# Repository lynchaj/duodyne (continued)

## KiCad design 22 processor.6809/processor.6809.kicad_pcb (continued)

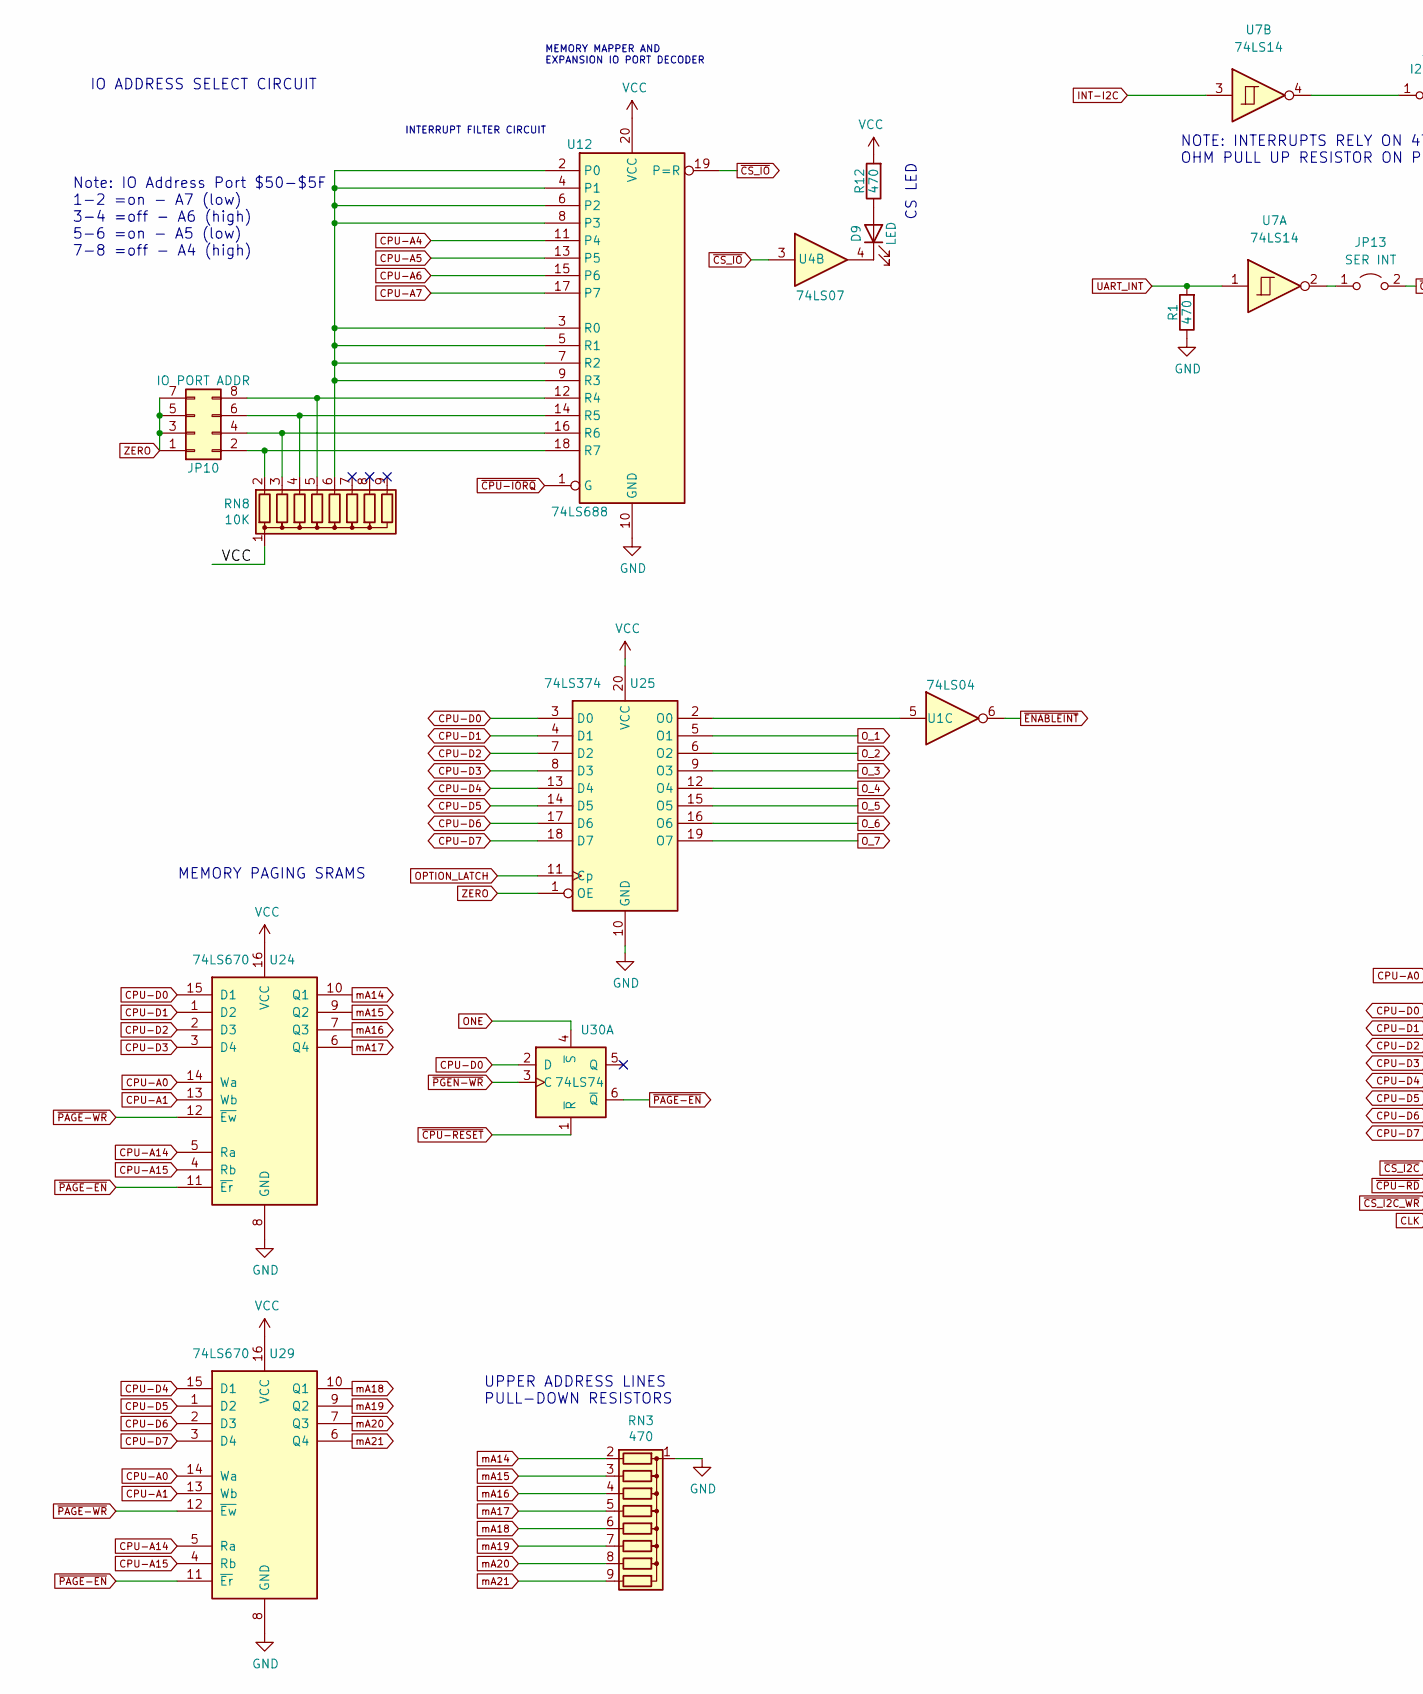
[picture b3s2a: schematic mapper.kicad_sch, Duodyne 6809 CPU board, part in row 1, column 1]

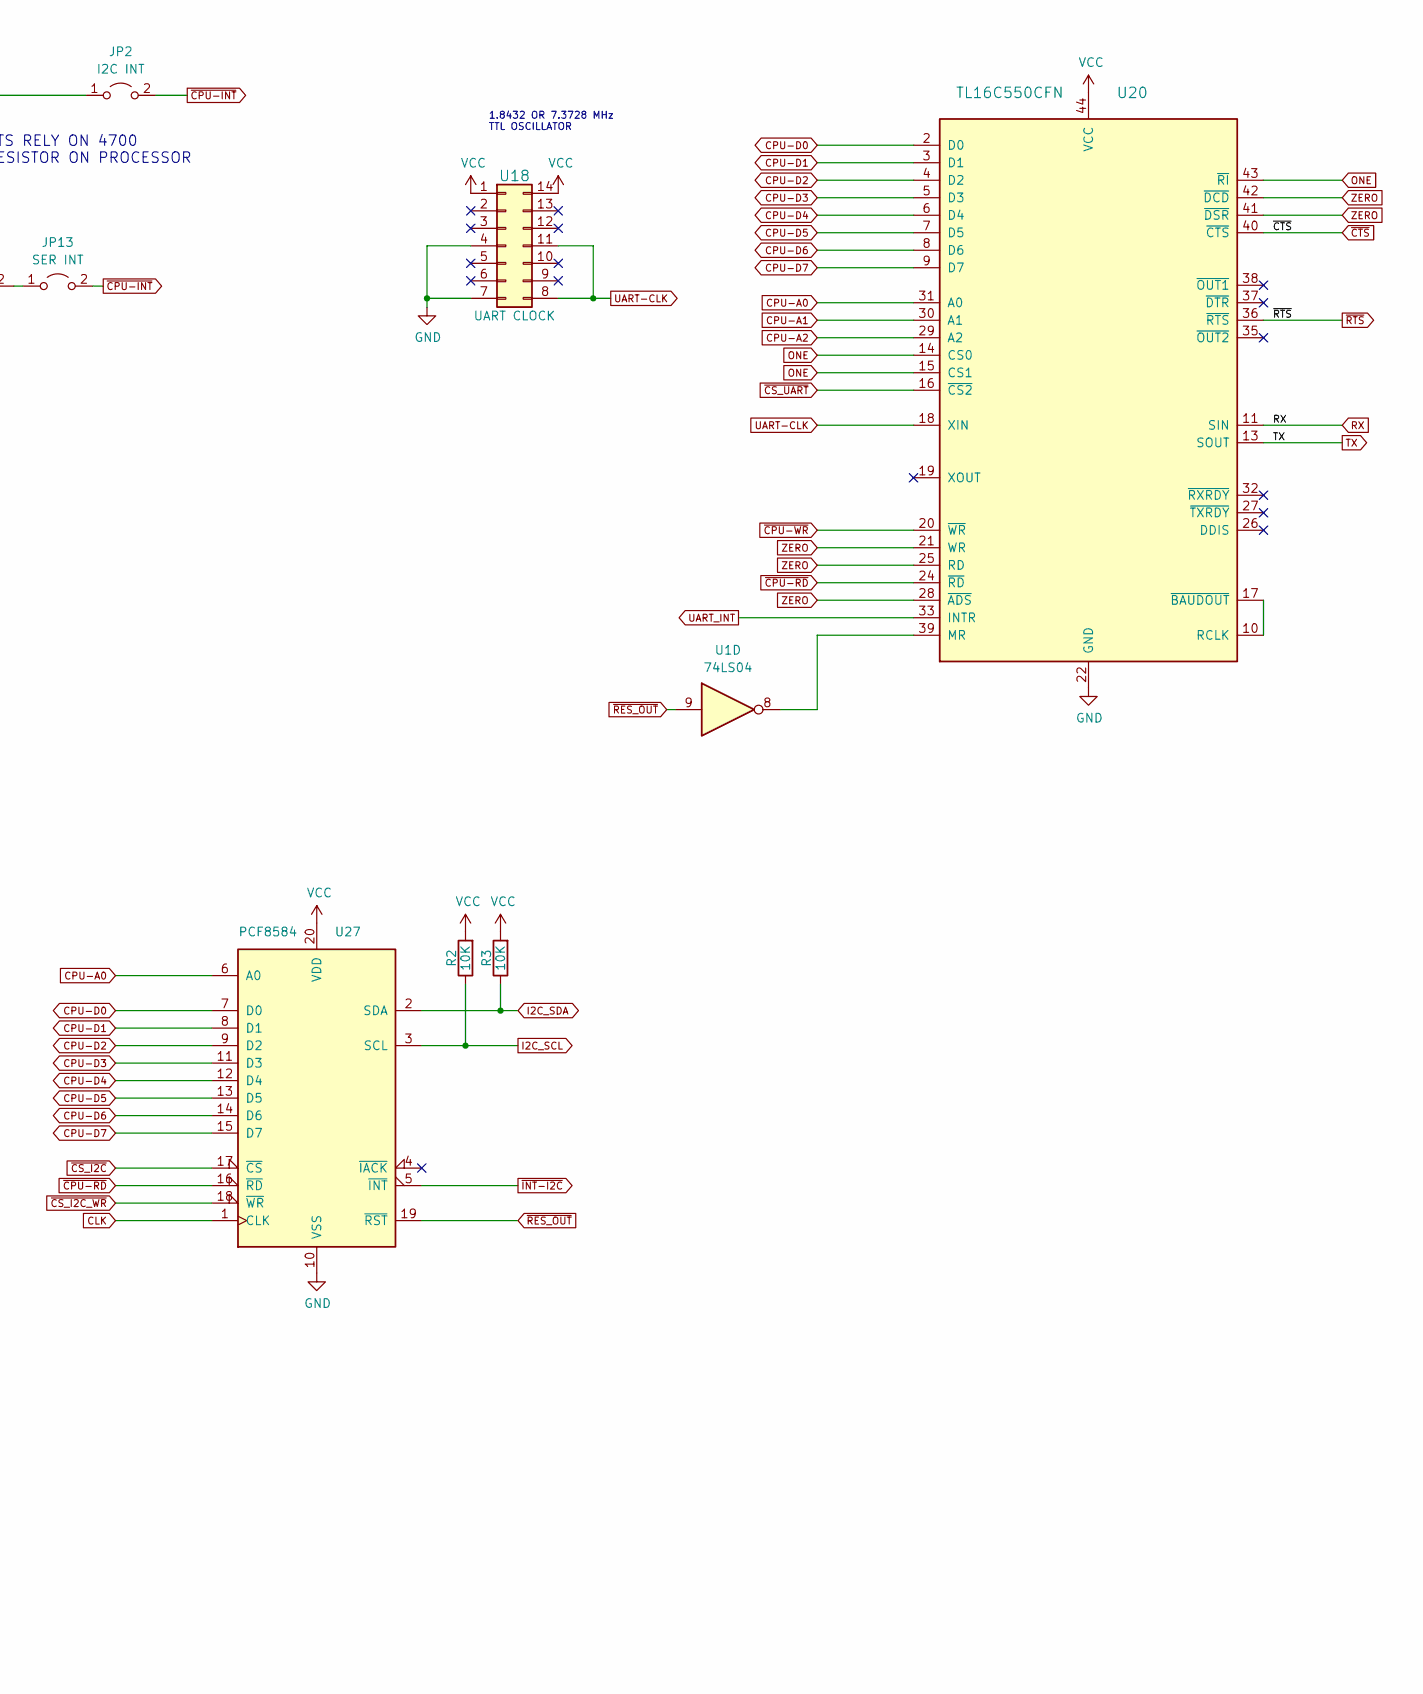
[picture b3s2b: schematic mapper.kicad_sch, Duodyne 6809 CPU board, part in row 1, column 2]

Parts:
D9: LED; LED_D3.0mm_Horizontal_O3.81mm_Z2.0mm
JP2: I2C INT; PinHeader_1x02_P2.54mm_Vertical
JP10: IO PORT ADDR; PinHeader_2x04_P2.54mm_Vertical
JP13: SER INT; PinHeader_1x02_P2.54mm_Vertical
R1, R12: 470; R_Axial_DIN0207_L6.3mm_D2.5mm_P7.62mm_Horizontal
R2, R3: 10K; R_Axial_DIN0207_L6.3mm_D2.5mm_P7.62mm_Horizontal
RN3: 470; R_Array_SIP9
RN8: 10K; R_Array_SIP9
U1: 74LS04; DIP-14_W7.62mm_Socket_LongPads
U4: 74LS07; DIP-14_W7.62mm_Socket_LongPads
U7: 74LS14; DIP-14_W7.62mm_Socket_LongPads
U12: 74LS688; DIP-20_W7.62mm_Socket_LongPads
U18: UART CLOCK; DIP-14_W7.62mm_Socket_LongPads
U20: TL16C550CFN; PLCC-44_THT-Socket
U24, U29: 74LS670; DIP-16_W7.62mm
U25: 74LS374; DIP-20_W7.62mm_Socket_LongPads
U27: PCF8584; DIP-20_W7.62mm_Socket_LongPads
U30: 74LS74; DIP-14_W7.62mm

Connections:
CLK: U27.1 (CLK); also elsewhere on the board
CPU-A0: U20.31 (A0), U24.14 (Wa), U27.6 (A0), U29.14 (Wa); also elsewhere on the board
CPU-A1: U20.30 (A1), U24.13 (Wb), U29.13 (Wb); also elsewhere on the board
CPU-A2: U20.29 (A2); also elsewhere on the board
CPU-A4: U12.11 (P4); also elsewhere on the board
CPU-A5: U12.13 (P5); also elsewhere on the board
CPU-A6: U12.15 (P6); also elsewhere on the board
CPU-A7: U12.17 (P7); also elsewhere on the board
CPU-A14: U24.5 (Ra), U29.5 (Ra); also elsewhere on the board
CPU-A15: U24.4 (Rb), U29.4 (Rb); also elsewhere on the board
CPU-D0: U20.2 (D0), U24.15 (D1), U25.3 (D0), U27.7 (D0), U30.2 (D); also elsewhere on the board
CPU-D1: U20.3 (D1), U24.1 (D2), U25.4 (D1), U27.8 (D1); also elsewhere on the board
CPU-D2: U20.4 (D2), U24.2 (D3), U25.7 (D2), U27.9 (D2); also elsewhere on the board
CPU-D3: U20.5 (D3), U24.3 (D4), U25.8 (D3), U27.11 (D3); also elsewhere on the board
CPU-D4: U20.6 (D4), U25.13 (D4), U27.12 (D4), U29.15 (D1); also elsewhere on the board
CPU-D5: U20.7 (D5), U25.14 (D5), U27.13 (D5), U29.1 (D2); also elsewhere on the board
CPU-D6: U20.8 (D6), U25.17 (D6), U27.14 (D6), U29.2 (D3); also elsewhere on the board
CPU-D7: U20.9 (D7), U25.18 (D7), U27.15 (D7), U29.3 (D4); also elsewhere on the board
GND: R1.1, RN3.1 (common), U12.10 (GND), U18.4, U18.7, U20.22 (GND), U24.8 (GND), U25.10 (GND), U27.10 (VSS), U29.8 (GND); also elsewhere on the board
I2C_SCL: R2.1, U27.3 (SCL); also elsewhere on the board
I2C_SDA: R3.1, U27.2 (SDA); also elsewhere on the board
INT-I2C: U7.3; also elsewhere on the board
unnamed: D9.1 (K), U4.4
unnamed: D9.2 (A), R12.1
unnamed: JP2.1 (A), U7.4
unnamed: JP10.2, RN8.2 (R1), U12.18 (R7)
unnamed: JP10.4, RN8.3 (R2), U12.16 (R6)
unnamed: JP10.6, RN8.4 (R3), U12.14 (R5)
unnamed: JP10.8, RN8.5 (R4), U12.12 (R4)
unnamed: JP13.1 (A), U7.2
unnamed: RN8.6 (R5), U12.2 (P0), U12.3 (R0), U12.4 (P1), U12.5 (R1), U12.6 (P2), U12.7 (R2), U12.8 (P3), U12.9 (R3)
unnamed: U1.5, U25.2 (O0)
unnamed: U1.8, U20.39 (MR)
unnamed: U20.10 (RCLK), U20.17 (~BAUDOUT)
ONE: U20.14 (CS0), U20.15 (CS1), U20.43 (~RI), U30.4 (~S); also elsewhere on the board
OPTION_LATCH: U25.11 (Cp); also elsewhere on the board
O_1: U25.5 (O1); also elsewhere on the board
O_2: U25.6 (O2); also elsewhere on the board
O_3: U25.9 (O3); also elsewhere on the board
O_4: U25.12 (O4); also elsewhere on the board
O_5: U25.15 (O5); also elsewhere on the board
O_6: U25.16 (O6); also elsewhere on the board
O_7: U25.19 (O7); also elsewhere on the board
RX: U20.11 (SIN); also elsewhere on the board
TX: U20.13 (SOUT); also elsewhere on the board
UART-CLK: U18.8, U18.11, U20.18 (XIN)
UART_INT: R1.2, U7.1, U20.33 (INTR)
VCC: R2.2, R3.2, R12.2, RN8.1 (common), U12.20 (VCC), U18.1, U18.14, U20.44 (VCC), U24.16 (VCC), U25.20 (VCC), U27.20 (VDD), U29.16 (VCC); also elsewhere on the board
ZERO: JP10.1, JP10.3, JP10.5, JP10.7, U20.21 (WR), U20.25 (RD), U20.28 (~ADS), U20.41 (~DSR), U20.42 (~DCD), U25.1 (OE); also elsewhere on the board
mA14: RN3.2 (R1), U24.10 (Q1); also elsewhere on the board
mA15: RN3.3 (R2), U24.9 (Q2); also elsewhere on the board
mA16: RN3.4 (R3), U24.7 (Q3); also elsewhere on the board
mA17: RN3.5 (R4), U24.6 (Q4); also elsewhere on the board
mA18: RN3.6 (R5), U29.10 (Q1); also elsewhere on the board
mA19: RN3.7 (R6), U29.9 (Q2); also elsewhere on the board
mA20: RN3.8 (R7), U29.7 (Q3); also elsewhere on the board
mA21: RN3.9 (R8), U29.6 (Q4); also elsewhere on the board
~CPU-INT: JP2.2 (B), JP13.2 (B); also elsewhere on the board
~CPU-IORQ: U12.1 (G); also elsewhere on the board
~CPU-RD: U20.24 (~RD), U27.16 (~RD); also elsewhere on the board
~CPU-RESET: U30.1 (~R); also elsewhere on the board
~CPU-WR: U20.20 (~WR); also elsewhere on the board
~CS_I2C_WR: U27.18 (~WR); also elsewhere on the board
~CS_I2C: U27.17 (~CS); also elsewhere on the board
~CS_IO: U4.3, U12.19 (P=R); also elsewhere on the board
~CS_UART: U20.16 (~CS2); also elsewhere on the board
~CTS: U20.40 (~CTS); also elsewhere on the board
~ENABLEINT: U1.6; also elsewhere on the board
~INT-I2C: U27.5 (~INT); also elsewhere on the board
~PAGE-EN: U24.11 (~Er), U29.11 (~Er), U30.6 (~Q); also elsewhere on the board
~PAGE-WR: U24.12 (~Ew), U29.12 (~Ew); also elsewhere on the board
~PGEN-WR: U30.3 (C); also elsewhere on the board
~RES_OUT: U1.9, U27.19 (~RST); also elsewhere on the board
~RTS: U20.36 (~RTS); also elsewhere on the board

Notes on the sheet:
MEMORY MAPPER AND EXPANSION IO PORT DECODER
CS LED
IO ADDRESS SELECT CIRCUIT
INTERRUPT FILTER CIRCUIT
NOTE: INTERRUPTS RELY ON 4700 OHM PULL UP RESISTOR ON PROCESSOR
Note: IO Address Port $50-$5F 1-2 =on - A7 (low) 3-4 =off - A6 (high) 5-6 =on - A5 (low) 7-8 =off - A4 (high)
MEMORY PAGING SRAMS
1.8432 OR 7.3728 MHz TTL OSCILLATOR
UPPER ADDRESS LINES PULL-DOWN RESISTORS

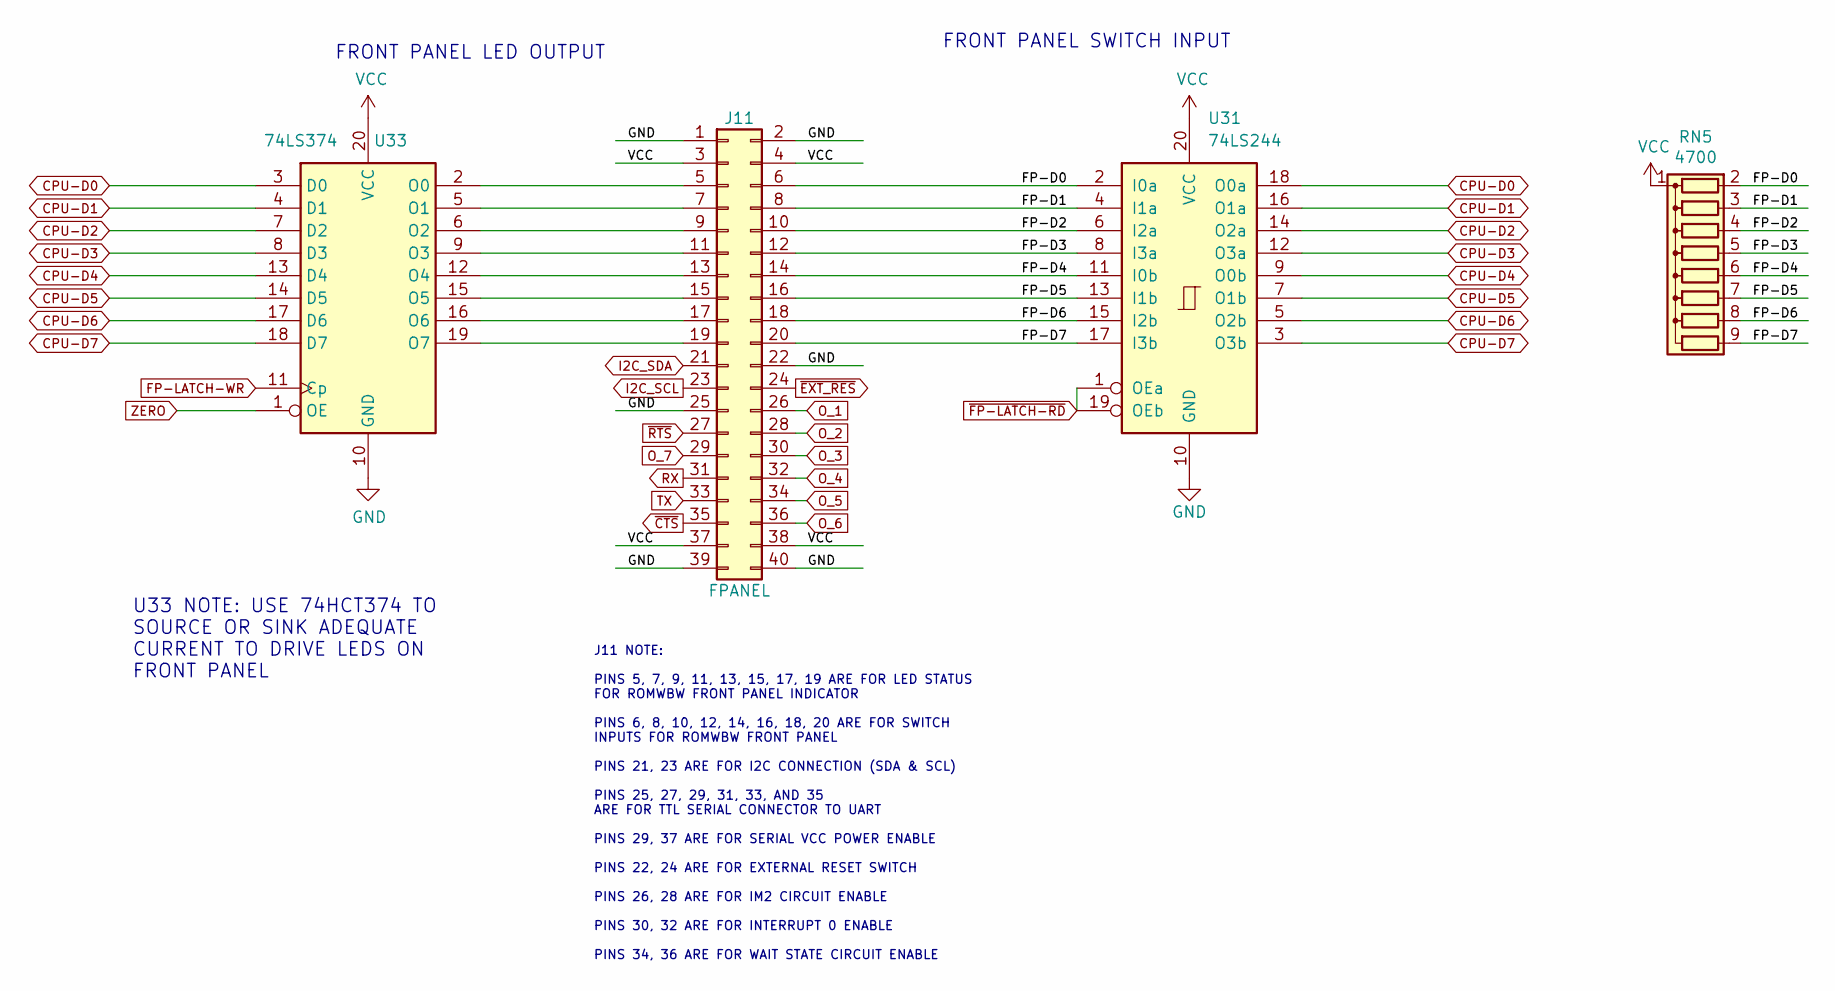
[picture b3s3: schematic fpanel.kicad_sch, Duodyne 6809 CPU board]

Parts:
J11: FPANEL; IDC-Header_2x20_P2.54mm_Horizontal
RN5: 4700; R_Array_SIP9
U31: 74LS244; DIP-20_W7.62mm_Socket_LongPads
U33: 74LS374; DIP-20_W7.62mm_Socket_LongPads

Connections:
/fpanel/FP-D0: J11.6, RN5.2 (R1), U31.2 (I0a)
/fpanel/FP-D1: J11.8, RN5.3 (R2), U31.4 (I1a)
/fpanel/FP-D2: J11.10, RN5.4 (R3), U31.6 (I2a)
/fpanel/FP-D3: J11.12, RN5.5 (R4), U31.8 (I3a)
/fpanel/FP-D4: J11.14, RN5.6 (R5), U31.11 (I0b)
/fpanel/FP-D5: J11.16, RN5.7 (R6), U31.13 (I1b)
/fpanel/FP-D6: J11.18, RN5.8 (R7), U31.15 (I2b)
/fpanel/FP-D7: J11.20, RN5.9 (R8), U31.17 (I3b)
CPU-D0: U31.18 (O0a), U33.3 (D0); also elsewhere on the board
CPU-D1: U31.16 (O1a), U33.4 (D1); also elsewhere on the board
CPU-D2: U31.14 (O2a), U33.7 (D2); also elsewhere on the board
CPU-D3: U31.12 (O3a), U33.8 (D3); also elsewhere on the board
CPU-D4: U31.9 (O0b), U33.13 (D4); also elsewhere on the board
CPU-D5: U31.7 (O1b), U33.14 (D5); also elsewhere on the board
CPU-D6: U31.5 (O2b), U33.17 (D6); also elsewhere on the board
CPU-D7: U31.3 (O3b), U33.18 (D7); also elsewhere on the board
FP-LATCH-WR: U33.11 (Cp); also elsewhere on the board
GND: J11.1, J11.2, J11.22, J11.25, J11.39, J11.40, U31.10 (GND), U33.10 (GND); also elsewhere on the board
I2C_SCL: J11.23; also elsewhere on the board
I2C_SDA: J11.21; also elsewhere on the board
unnamed: J11.5, U33.2 (O0)
unnamed: J11.7, U33.5 (O1)
unnamed: J11.9, U33.6 (O2)
unnamed: J11.11, U33.9 (O3)
unnamed: J11.13, U33.12 (O4)
unnamed: J11.15, U33.15 (O5)
unnamed: J11.17, U33.16 (O6)
unnamed: J11.19, U33.19 (O7)
O_1: J11.26; also elsewhere on the board
O_2: J11.28; also elsewhere on the board
O_3: J11.30; also elsewhere on the board
O_4: J11.32; also elsewhere on the board
O_5: J11.34; also elsewhere on the board
O_6: J11.36; also elsewhere on the board
O_7: J11.29; also elsewhere on the board
RX: J11.31; also elsewhere on the board
TX: J11.33; also elsewhere on the board
VCC: J11.3, J11.4, J11.37, J11.38, RN5.1 (common), U31.20 (VCC), U33.20 (VCC); also elsewhere on the board
ZERO: U33.1 (OE); also elsewhere on the board
~CTS: J11.35; also elsewhere on the board
~EXT_RES: J11.24; also elsewhere on the board
~FP-LATCH-RD: U31.1 (OEa), U31.19 (OEb); also elsewhere on the board
~RTS: J11.27; also elsewhere on the board

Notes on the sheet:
J11 NOTE: PINS 5, 7, 9, 11, 13, 15, 17, 19 ARE FOR LED STATUS FOR ROMWBW FRONT PANEL INDICATOR PINS 6, 8, 10, 12, 14, 16, 18, 20 ARE FOR SWITCH INPUTS FOR ROMWBW FRONT PANEL PINS 21, 23 ARE FOR I2C CONNECTION (SDA & SCL) PINS 25, 27, 29, 31, 33, AND 35 ARE FOR TTL SERIAL CONNECTOR TO UART PINS 29, 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
U33 NOTE: USE 74HCT374 TO SOURCE OR SINK ADEQUATE CURRENT TO DRIVE LEDS ON FRONT PANEL
FRONT PANEL SWITCH INPUT
FRONT PANEL LED OUTPUT

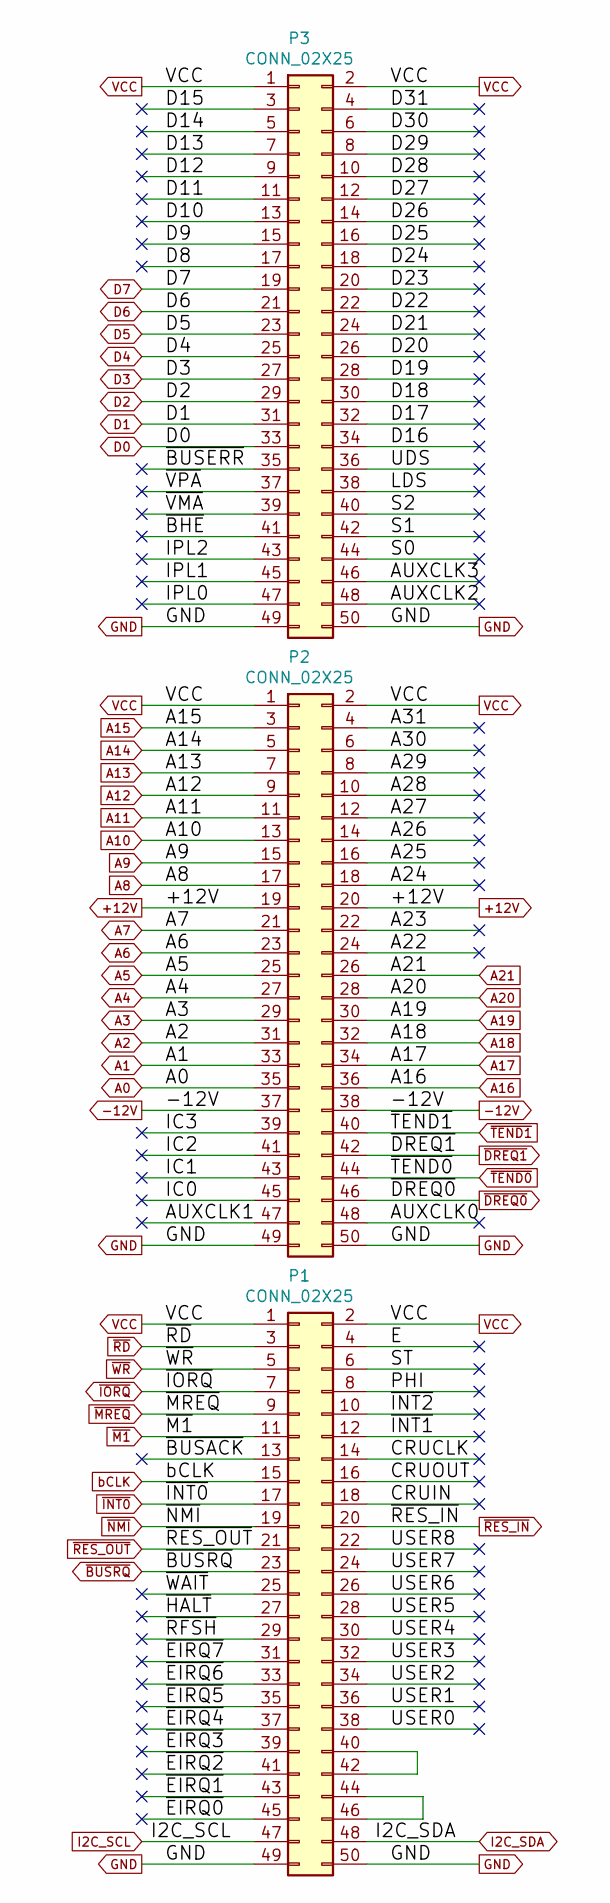
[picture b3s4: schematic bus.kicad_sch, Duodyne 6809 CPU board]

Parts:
P1, P2, P3: CONN_02X25; IDC-Header_2x25_P2.54mm_Horizontal

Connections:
+12V: P2.19, P2.20
-12V: P2.37, P2.38
/bus/A22: P2.24
/bus/A23: P2.22
/bus/A24: P2.18
/bus/A25: P2.16
/bus/A26: P2.14
/bus/A27: P2.12
/bus/A28: P2.10
/bus/A29: P2.8
/bus/A30: P2.6
/bus/A31: P2.4
/bus/AUXCLK0: P2.48
/bus/AUXCLK1: P2.47
/bus/AUXCLK2: P3.48
/bus/AUXCLK3: P3.46
/bus/CRUCLK: P1.14
/bus/CRUIN: P1.18
/bus/CRUOUT: P1.16
/bus/D8: P3.17
/bus/D9: P3.15
/bus/D10: P3.13
/bus/D11: P3.11
/bus/D12: P3.9
/bus/D13: P3.7
/bus/D14: P3.5
/bus/D15: P3.3
/bus/D16: P3.34
/bus/D17: P3.32
/bus/D18: P3.30
/bus/D19: P3.28
/bus/D20: P3.26
/bus/D21: P3.24
/bus/D22: P3.22
/bus/D23: P3.20
/bus/D24: P3.18
/bus/D25: P3.16
/bus/D26: P3.14
/bus/D27: P3.12
/bus/D28: P3.10
/bus/D29: P3.8
/bus/D30: P3.6
/bus/D31: P3.4
/bus/E: P1.4
/bus/IC0: P2.45
/bus/IC1: P2.43
/bus/IC2: P2.41
/bus/IC3: P2.39
/bus/IPL0: P3.47
/bus/IPL1: P3.45
/bus/IPL2: P3.43
/bus/LDS: P3.38
/bus/PHI: P1.8
/bus/S0: P3.44
/bus/S1: P3.42
/bus/S2: P3.40
/bus/ST: P1.6
/bus/UDS: P3.36
/bus/USER0: P1.38
/bus/USER1: P1.36
/bus/USER2: P1.34
/bus/USER3: P1.32
/bus/USER4: P1.30
/bus/USER5: P1.28
/bus/USER6: P1.26
/bus/USER7: P1.24
/bus/USER8: P1.22
/bus/~BHE: P3.41
/bus/~BUSACK: P1.13
/bus/~BUSERR: P3.35
/bus/~EIRQ0: P1.45
/bus/~EIRQ1: P1.43
/bus/~EIRQ2: P1.41
/bus/~EIRQ3: P1.39
/bus/~EIRQ4: P1.37
/bus/~EIRQ5: P1.35
/bus/~EIRQ6: P1.33
/bus/~EIRQ7: P1.31
/bus/~HALT: P1.27
/bus/~INT1: P1.12
/bus/~INT2: P1.10
/bus/~RFSH: P1.29
/bus/~VMA: P3.39
/bus/~VPA: P3.37
/bus/~WAIT: P1.25
A0: P2.35; also elsewhere on the board
A1: P2.33; also elsewhere on the board
A2: P2.31; also elsewhere on the board
A3: P2.29; also elsewhere on the board
A4: P2.27; also elsewhere on the board
A5: P2.25; also elsewhere on the board
A6: P2.23; also elsewhere on the board
A7: P2.21; also elsewhere on the board
A8: P2.17; also elsewhere on the board
A9: P2.15; also elsewhere on the board
A10: P2.13; also elsewhere on the board
A11: P2.11; also elsewhere on the board
A12: P2.9; also elsewhere on the board
A13: P2.7; also elsewhere on the board
A14: P2.5; also elsewhere on the board
A15: P2.3; also elsewhere on the board
A16: P2.36; also elsewhere on the board
A17: P2.34; also elsewhere on the board
A18: P2.32; also elsewhere on the board
A19: P2.30; also elsewhere on the board
A20: P2.28; also elsewhere on the board
A21: P2.26; also elsewhere on the board
D0: P3.33; also elsewhere on the board
D1: P3.31; also elsewhere on the board
D2: P3.29; also elsewhere on the board
D3: P3.27; also elsewhere on the board
D4: P3.25; also elsewhere on the board
D5: P3.23; also elsewhere on the board
D6: P3.21; also elsewhere on the board
D7: P3.19; also elsewhere on the board
GND: P1.49, P1.50, P2.49, P2.50, P3.49, P3.50; also elsewhere on the board
I2C_SCL: P1.47; also elsewhere on the board
I2C_SDA: P1.48; also elsewhere on the board
unnamed: P1.40, P1.42
unnamed: P1.44, P1.46
VCC: P1.1, P1.2, P2.1, P2.2, P3.1, P3.2; also elsewhere on the board
bCLK: P1.15; also elsewhere on the board
~BUSRQ: P1.23; also elsewhere on the board
~DREQ0: P2.46; also elsewhere on the board
~DREQ1: P2.42; also elsewhere on the board
~INT0: P1.17; also elsewhere on the board
~IORQ: P1.7; also elsewhere on the board
~M1: P1.11; also elsewhere on the board
~MREQ: P1.9; also elsewhere on the board
~NMI: P1.19; also elsewhere on the board
~RD: P1.3; also elsewhere on the board
~RES_IN: P1.20; also elsewhere on the board
~RES_OUT: P1.21; also elsewhere on the board
~TEND0: P2.44; also elsewhere on the board
~TEND1: P2.40; also elsewhere on the board
~WR: P1.5; also elsewhere on the board

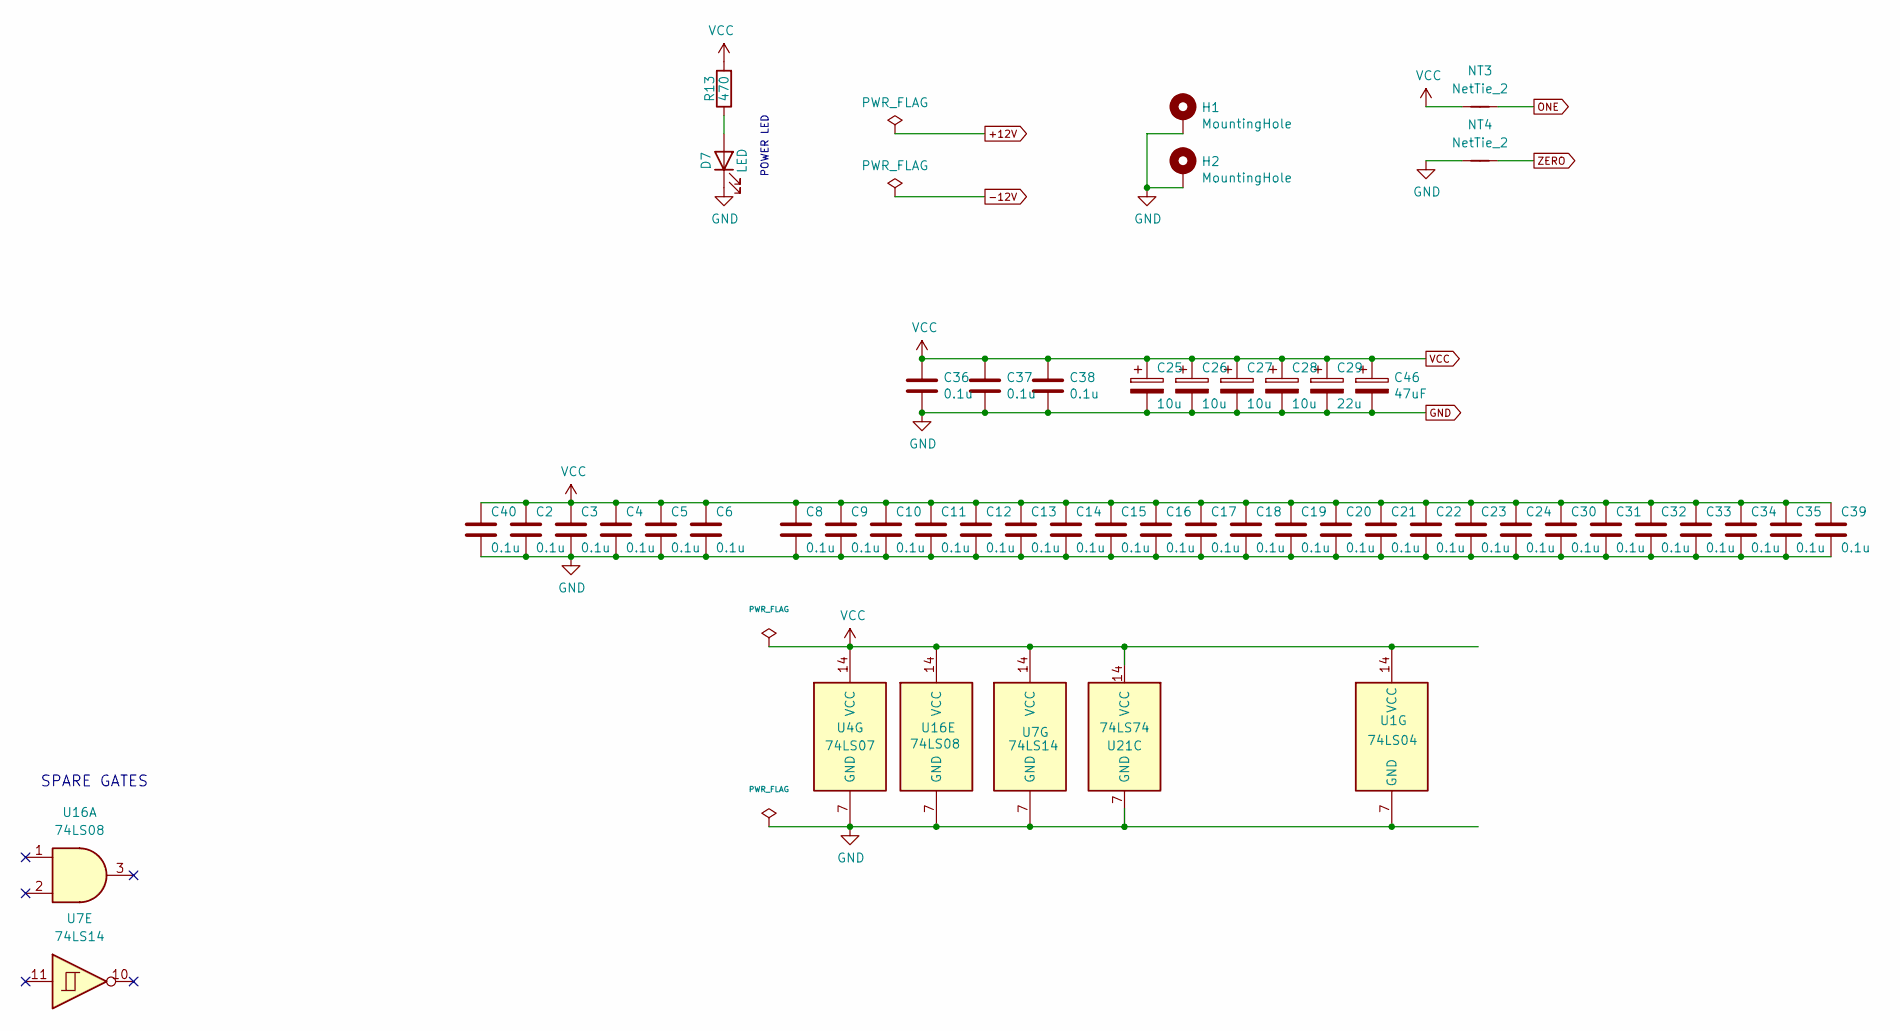
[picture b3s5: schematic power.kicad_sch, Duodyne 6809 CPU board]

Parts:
C2, C3, C4, C5, C6, C8, C9, C10, C11, C12, C13, C14, C15, C16, C17, C18, C19, C20, C21, C22, C23, C24, C30, C31, C32, C33, C34, C35, C36, C37, C38, C39, C40: 0.1u; C_Disc_D5.0mm_W2.5mm_P5.00mm
C25, C26, C27, C28: 10u; CP_Radial_D5.0mm_P2.50mm
C29: 22u; CP_Radial_D5.0mm_P2.50mm
C46: 47uF; CP_Radial_D5.0mm_P2.50mm
D7: LED; LED_D3.0mm_Horizontal_O3.81mm_Z2.0mm
H1, H2: MountingHole; MountingHole_3.2mm_M3_Pad
NT3, NT4: NetTie_2; NetTie-2_THT_Pad0.3mm
R13: 470; R_Axial_DIN0207_L6.3mm_D2.5mm_P7.62mm_Horizontal
U1: 74LS04; DIP-14_W7.62mm_Socket_LongPads
U4: 74LS07; DIP-14_W7.62mm_Socket_LongPads
U7: 74LS14; DIP-14_W7.62mm_Socket_LongPads
U16: 74LS08; DIP-14_W7.62mm_Socket_LongPads
U21: 74LS74; DIP-14_W7.62mm_Socket_LongPads

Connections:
GND: C2.2, C3.2, C4.2, C5.2, C6.2, C8.2, C9.2, C10.2, C11.2, C12.2, C13.2, C14.2, C15.2, C16.2, C17.2, C18.2, C19.2, C20.2, C21.2, C22.2, C23.2, C24.2, C25.2, C26.2, C27.2, C28.2, C29.2, C30.2, C31.2, C32.2, C33.2, C34.2, C35.2, C36.2, C37.2, C38.2, C39.2, C40.2, C46.2, D7.1 (K), H1.1, H2.1, NT4.1, U1.7 (GND), U4.7 (GND), U7.7 (GND), U16.7 (GND), U21.7 (GND); also elsewhere on the board
unnamed: D7.2 (A), R13.1
ONE: NT3.2; also elsewhere on the board
VCC: C2.1, C3.1, C4.1, C5.1, C6.1, C8.1, C9.1, C10.1, C11.1, C12.1, C13.1, C14.1, C15.1, C16.1, C17.1, C18.1, C19.1, C20.1, C21.1, C22.1, C23.1, C24.1, C25.1, C26.1, C27.1, C28.1, C29.1, C30.1, C31.1, C32.1, C33.1, C34.1, C35.1, C36.1, C37.1, C38.1, C39.1, C40.1, C46.1, NT3.1, R13.2, U1.14 (VCC), U4.14 (VCC), U7.14 (VCC), U16.14 (VCC), U21.14 (VCC); also elsewhere on the board
ZERO: NT4.2; also elsewhere on the board

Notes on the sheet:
POWER LED
SPARE GATES
